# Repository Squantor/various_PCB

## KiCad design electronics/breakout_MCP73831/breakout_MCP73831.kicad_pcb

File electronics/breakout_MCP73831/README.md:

# MCP73831/2 breakout
Small breakout board for the MCP73831 or MCP73832 LiIon charging IC.
## TODO's
Still some things need to be done:
* Review with one night in between
* Produce
* Assemble
* Test & characterise
* update Readme.md with pictures and BOM
## BOM
* MCP73831
* 1206 10uF ceramic caps

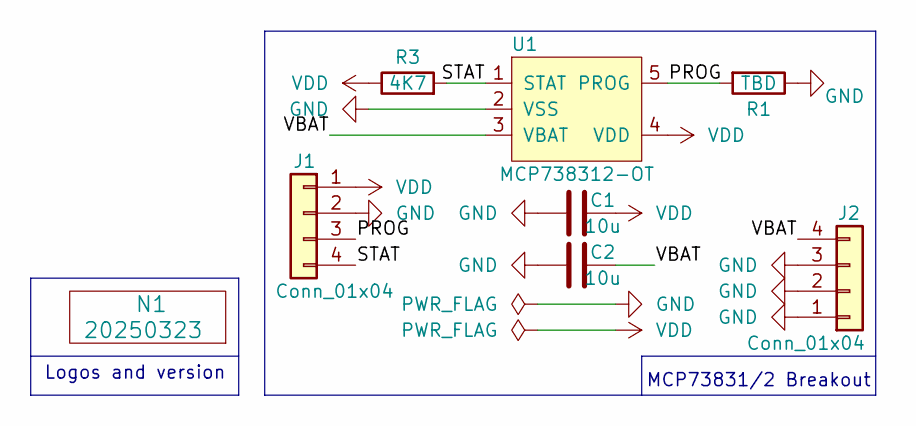
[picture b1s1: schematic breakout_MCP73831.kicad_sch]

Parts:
C1, C2: 10u; C_1206_0805
J1, J2: Conn_01x04; Header-0254-1X04-H010
N1: 20250323; Label_Generic
R1: TBD; R_0603_hand
R3: 4K7; R_0603_hand
U1: MCP738312-OT; SOT23-5-Microchip-OT

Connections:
/PROG: J1.3, R1.2, U1.5 (PROG)
/STAT: J1.4, R3.2, U1.1 (STAT)
/VBAT: C2.2, J2.4, U1.3 (VBAT)
GND: C1.1, C2.1, J1.2, J2.1, J2.2, J2.3, R1.1, U1.2 (VSS)
VDD: C1.2, J1.1, R3.1, U1.4 (VDD)

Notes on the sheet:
Logos and version
MCP73831/2 Breakout

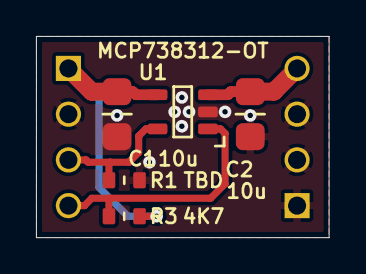
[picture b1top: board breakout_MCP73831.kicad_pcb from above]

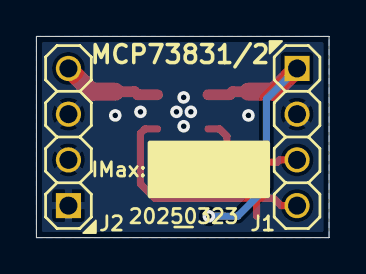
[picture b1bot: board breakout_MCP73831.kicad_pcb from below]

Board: 2 copper layers, 16.3 x 11.2 mm, 8 parts (3 on the bottom side), 5 nets.

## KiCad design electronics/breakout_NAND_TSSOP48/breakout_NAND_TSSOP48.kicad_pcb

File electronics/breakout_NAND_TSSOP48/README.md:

# Generic TSSOP48 NAND breakout
Simple breakout board for TSSOP48 NAND chips
## TODO's
Still some things need to be done:
* PCB layout
* Review with one night in between
* Produce
* Assemble
* Test & characterise
* update Readme.md with pictures and BOM
## BOM
* Any TSSOP48 NAND should fit

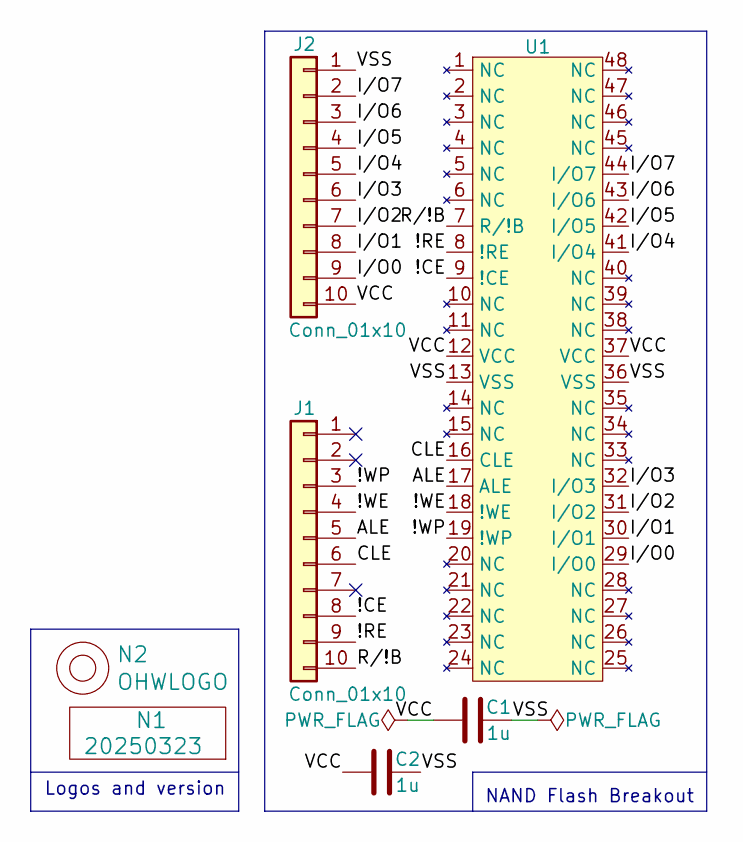
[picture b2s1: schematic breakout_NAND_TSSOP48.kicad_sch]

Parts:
C1, C2: 1u; C_0603
J1, J2: Conn_01x10; Header-0254-1X10-H010
N1: 20250323; Label_Generic
N2: OHWLOGO; OSHW-Symbol_6.7x6mm_SilkScreen
U1: TSOP-I-48_18.4x12mm_P0.5mm

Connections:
/!CE: J1.8, U1.9 (!CE)
/!RE: J1.9, U1.8 (!RE)
/!WE: J1.4, U1.18 (!WE)
/!WP: J1.3, U1.19 (!WP)
/ALE: J1.5, U1.17 (ALE)
/CLE: J1.6, U1.16 (CLE)
/I/O0: J2.9, U1.29 (I/O0)
/I/O1: J2.8, U1.30 (I/O1)
/I/O2: J2.7, U1.31 (I/O2)
/I/O3: J2.6, U1.32 (I/O3)
/I/O4: J2.5, U1.41 (I/O4)
/I/O5: J2.4, U1.42 (I/O5)
/I/O6: J2.3, U1.43 (I/O6)
/I/O7: J2.2, U1.44 (I/O7)
/R/!B: J1.10, U1.7 (R/!B)
/VCC: C1.1, C2.1, J2.10, U1.12 (VCC), U1.37 (VCC)
/VSS: C1.2, C2.2, J2.1, U1.13 (VSS), U1.36 (VSS)

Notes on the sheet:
NAND Flash Breakout
Logos and version

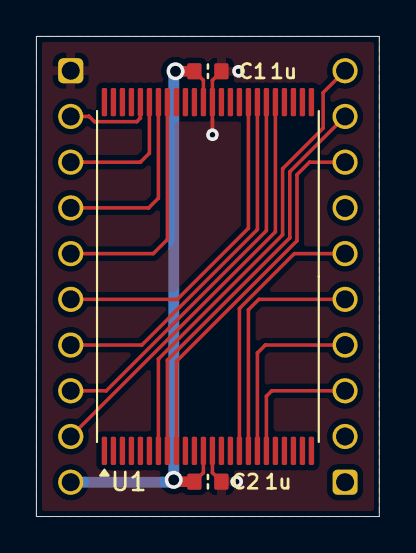
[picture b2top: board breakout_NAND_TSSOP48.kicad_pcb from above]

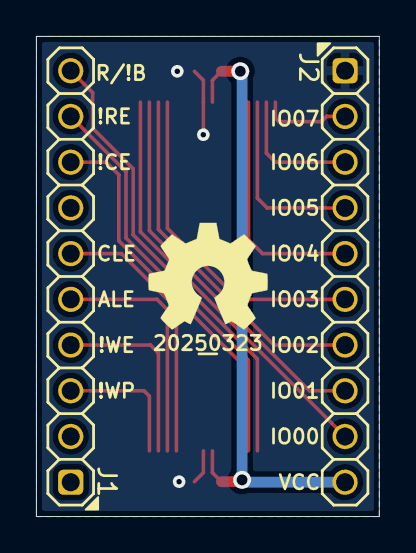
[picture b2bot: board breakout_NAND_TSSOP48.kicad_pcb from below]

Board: 2 copper layers, 19.1 x 26.7 mm, 7 parts (4 on the bottom side), 17 nets.

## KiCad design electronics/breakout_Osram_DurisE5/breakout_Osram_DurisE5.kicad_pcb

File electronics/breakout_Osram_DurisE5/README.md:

# Breakout for Osram DURIS E 5 LED's
Simple breakout for the [Osram DURIS E 5](https://www.osram.com/os/products/product-promotions/led-for-general-lighting/duris_e.jsp) light emitting diodes.
## TODO's
Still some things need to be done:
* Review with one night in between
* Produce at [OSHPARK](https://oshpark.com/)
* Assemble
* Test & characterise
* update Readme.md with pictures and BOM
## BOM
Any Osram DURIS E 5 LED.

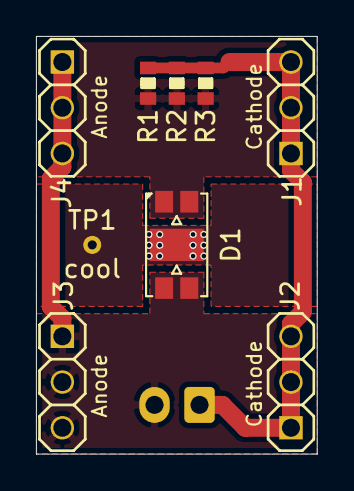
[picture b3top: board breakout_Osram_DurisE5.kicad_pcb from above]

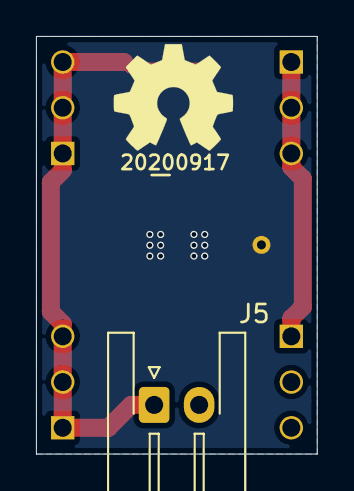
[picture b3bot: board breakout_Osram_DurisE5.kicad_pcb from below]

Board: 2 copper layers, 15.6 x 23.2 mm, 12 parts (3 on the bottom side), 4 nets.

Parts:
D1: LED; LED_5630
J1, J2, J3, J4: PINS_1X03; Header-0254-1X03-H010
J5: PINS_1X02; JST_XH_S2B-XH-A-1_1x02_P2.50mm_Horizontal
N1: 20200917; Label_Generic
N2: OHWLOGO; OSHW-Symbol_6.7x6mm_SilkScreen
R1, R2, R3: TBD; R_0603_hand
TP1: cool; TestPoint_hole_H05R10

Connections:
/Anode: D1.2, J3.1, J3.2, J3.3, J4.1, J4.2, J4.3, J5.2
/Cathode: J1.1, J1.2, J1.3, J2.1, J2.2, J2.3, J5.1, R1.2, R2.2, R3.2
/Cooling: D1.3, TP1.1
unnamed: D1.1, R1.1, R2.1, R3.1

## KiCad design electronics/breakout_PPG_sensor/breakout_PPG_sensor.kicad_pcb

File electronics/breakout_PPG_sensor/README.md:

# PPG components breakout
Small test project that places all the needed optical components for PPG ([photoplethysmogram](https://en.wikipedia.org/wiki/Photoplethysmogram)) sensor on a PCB. This includes the Green high brightness LED's and a visual range sensitivty photodiode. These components are usually in a housing that require cutouts in the PCB so they can sit flush with the other side. This breakout will test this.
## TODO's
Still some things need to be done:
* schematic entry (TODO)
* PCB layout (TODO)
* Review with one night in between (TODO)
* Produce at [OSHPARK](https://oshpark.com/) (TODO)
* Assemble (TODO)
* Test & characterise (TODO)
* update Readme.md with pictures and BOM (TODO)
## BOM
Used components:
* Kingbright [KPTR-3216ZGC](https://www.kingbright.com/attachments/file/psearch/000/00/00/KPTR-3216ZGC(Ver.12B).pdf) reverse mount 525nm (Green) LED.
* OSRAM [SFH 2440](https://www.osram.com/ecat/DIL%20SMT%20Ambient%20Light%20Sensor%20SFH%202440/com/en/class_pim_web_catalog_103489/global/prd_pim_device_2219615/) ambient light sensor.
## Pictures

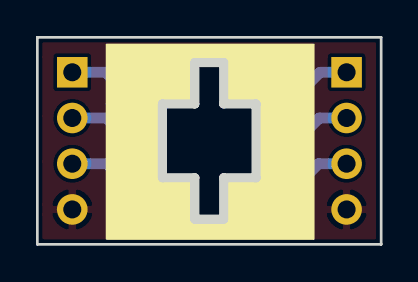
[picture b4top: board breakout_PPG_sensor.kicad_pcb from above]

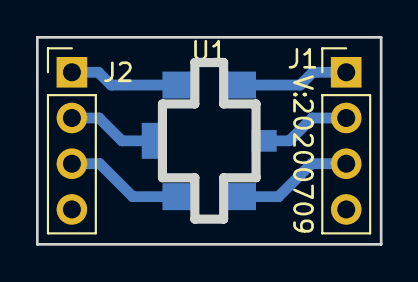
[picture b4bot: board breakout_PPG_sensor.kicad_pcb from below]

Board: 2 copper layers, 19.1 x 11.5 mm, 4 parts (3 on the bottom side), 7 nets.

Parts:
J1, J2: Conn_01x04; PinHeader_1x04_P2.54mm_Vertical
N2: 20200709; Label_version
U1: PPG_sensor; PPG_sensor_reverse

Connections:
/LED1_A: J1.3, U1.1
/LED1_C: J2.3, U1.6
/LED2_A: J1.1, U1.3
/LED2_C: J2.1, U1.4
/PD_A: J1.2, U1.2
/PD_C: J2.2, U1.5
/VSS: J1.4, J2.4
